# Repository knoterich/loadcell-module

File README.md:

## Loadcell Digitizer Module

The Loadcell Digitizer Module is a tool to interface wheatstone bridge loadcells over wifi.

The datalogging server can be founde here:https://github.com/knoterich/force-logger

# Specs

Samplerate: Two Modes (10Hz and 80Hz)
Precision: <1%
Accuracy: <1%
Excitation Voltage: 5V
Interface: UART 3V3 / Wifi 2.4Ghz WPA2

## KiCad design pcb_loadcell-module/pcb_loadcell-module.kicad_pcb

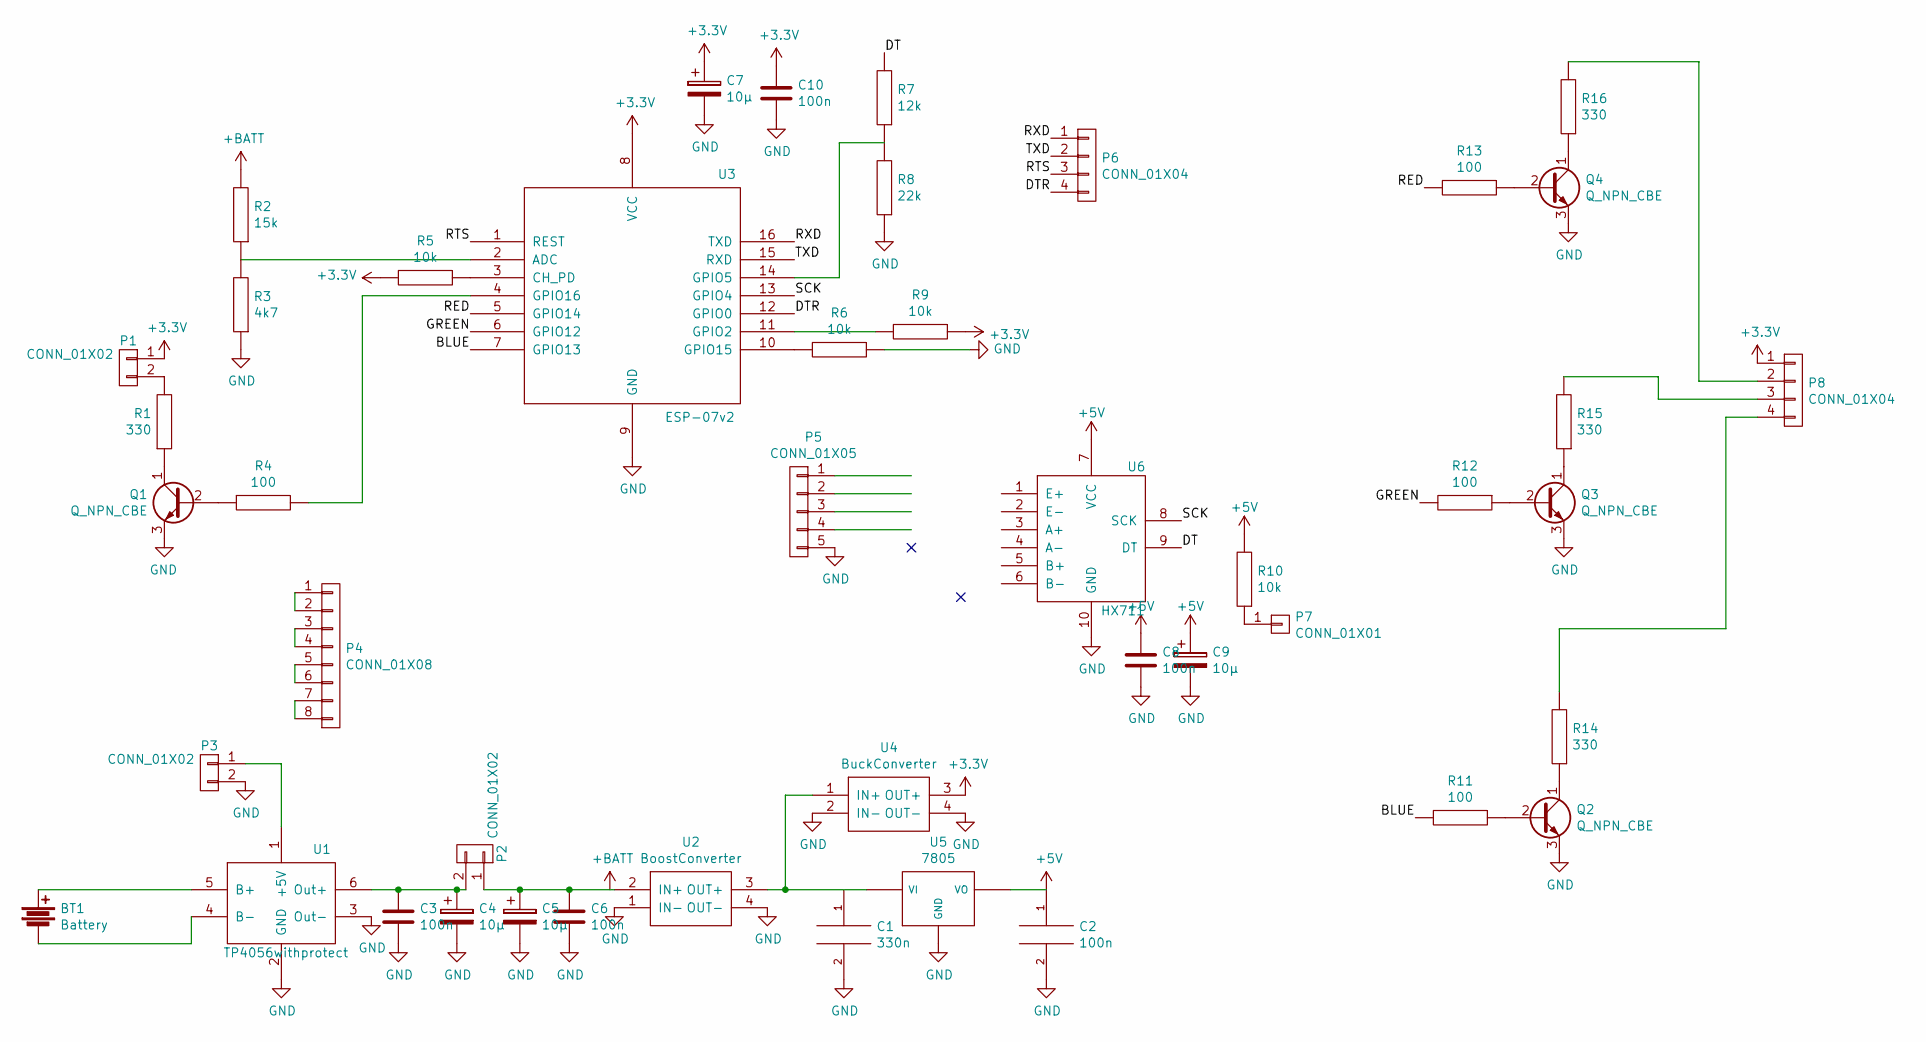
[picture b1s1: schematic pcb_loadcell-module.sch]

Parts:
BT1: Battery; 18650_bare
C1: 330n; C_Disc_D3_P2.5
C2, C3, C6, C8, C10: 100n; C_Disc_D3_P2.5
C4, C5, C7, C9: 10µ; C_Radial_D10_L13_P5
P1: CONN_01X02; Pin_Header_Straight_1x02
P2, P3: CONN_01X02; PhoenixContact_MCV-G_02x5.08mm_Vertical
P4: CONN_01X08; Pin_Header_Straight_2x04
P5: CONN_01X05; PhoenixContact_MCV-G_05x3.50mm_Vertical
P6: CONN_01X04; PhoenixContact_MCV-G_04x3.50mm_Vertical
P7: CONN_01X01; Pin_Header_Straight_1x01
P8: CONN_01X04; Pin_Header_Straight_1x04
Q1, Q2, Q3, Q4: Q_NPN_CBE; TO-92_Inline_Wide
R1, R14, R15, R16: 330; Resistor_Horizontal_RM10mm
R2: 15k; Resistor_Horizontal_RM10mm
R3: 4k7; Resistor_Horizontal_RM10mm
R4, R11, R12, R13: 100; Resistor_Horizontal_RM10mm
R5, R6, R9, R10: 10k; Resistor_Horizontal_RM10mm
R7: 12k; Resistor_Horizontal_RM10mm
R8: 22k; Resistor_Horizontal_RM10mm
U1: TP4056withprotect; TP4056_module_prot
U2: BoostConverter; MT3608_module_boost
U3: ESP-07v2
U4: BuckConverter; dsn-mini-360_buck
U5: 7805; TO-220_Neutral123_Horizontal
U6: HX711; hx711

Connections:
+3V3: C7.1, C10.1, P1.1, P8.1, R5.2, R9.1, U3.8 (VCC), U4.3 (OUT+)
+5V: C2.1, C8.1, C9.1, R10.2, U5.3 (VO), U6.7 (VCC)
+BATT: C5.1, C6.1, P2.1, R2.2, U2.2 (IN+)
/BLUE: R11.2, U3.7 (GPIO13)
/DT: R7.2, U6.9 (DT)
/DTR: P6.4, U3.12 (GPIO0)
/GREEN: R12.2, U3.6 (GPIO12)
/RED: R13.2, U3.5 (GPIO14)
/RTS: P6.3, U3.1 (REST)
/RXD: P6.1, U3.16 (TXD)
/SCK: U3.13 (GPIO4), U6.8 (SCK)
/TXD: P6.2, U3.15 (RXD)
GND: C1.2, C2.2, C3.2, C4.2, C5.2, C6.2, C7.2, C8.2, C9.2, C10.2, P3.2, P5.5, Q1.3 (E), Q2.3 (E), Q3.3 (E), Q4.3 (E), R3.1, R6.1, R8.1, U1.2 (GND), U1.3 (Out-), U2.1 (IN-), U2.4 (OUT-), U3.9 (GND), U4.2 (IN-), U4.4 (OUT-), U5.2 (GND), U6.10 (GND)
unnamed: BT1.+, U1.5 (B+)
unnamed: BT1.-, U1.4 (B-)
unnamed: C3.1, C4.1, P2.2, U1.6 (Out+)
unnamed: P1.2, R1.2
unnamed: P3.1, U1.1 (+5V)
unnamed: P4.1, P4.2
unnamed: P4.3, P4.4
unnamed: P4.5, P4.6
unnamed: P4.7, P4.8
unnamed: P5.1, U6.1 (E+)
unnamed: P5.2, U6.2 (E-)
unnamed: P5.3, U6.3 (A+)
unnamed: P5.4, U6.4 (A-)
unnamed: P7.1, R10.1
unnamed: P8.2, R16.2
unnamed: P8.3, R15.2
unnamed: P8.4, R14.2
unnamed: Q1.1 (C), R1.1
unnamed: Q1.2 (B), R4.1
unnamed: Q2.1 (C), R14.1
unnamed: Q2.2 (B), R11.1
unnamed: Q3.1 (C), R15.1
unnamed: Q3.2 (B), R12.1
unnamed: Q4.1 (C), R16.1
unnamed: Q4.2 (B), R13.1
unnamed: R2.1, R3.2, U3.2 (ADC)
unnamed: R4.2, U3.4 (GPIO16)
unnamed: R5.1, U3.3 (CH_PD)
unnamed: R6.2, U3.10 (GPIO15)
unnamed: R7.1, R8.2, U3.14 (GPIO5)
unnamed: R9.2, U3.11 (GPIO2)

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
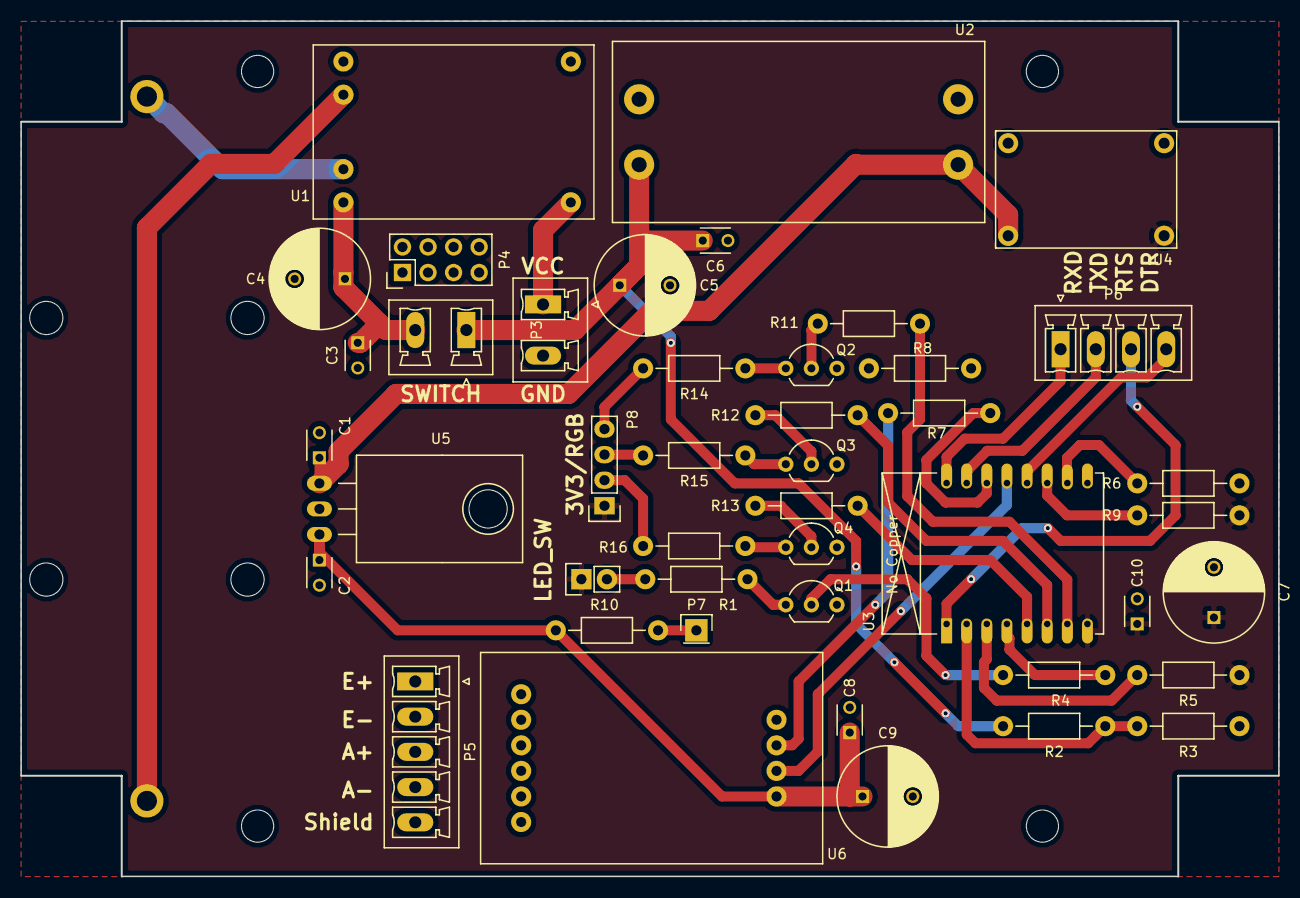
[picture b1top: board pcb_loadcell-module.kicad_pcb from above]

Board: 2 copper layers, 125.0 x 85.0 mm, 45 parts (1 on the bottom side), 45 nets.

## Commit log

2020-01-08 added initial files
2020-01-12 added non volative saving
2020-01-17 fixed serial configuration and added config output
